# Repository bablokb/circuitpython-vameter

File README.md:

Project circuitpython-vameter
=============================

News
----

  - 06/2025: added support for INA3221.<br>
    Changed configuration-setup (incompatible, see below)<br>
    Changed support for ESP-01S (see [ESP-01S logging HowTo](doc/esp01logger.md))
  - 02/2025: added support for recording gpio-state during sampling
  - 01/2025: added support for DataProvider-specific configuration screens
  - 02/2024: added support for logging to SD-card
  - 10/2023: added support for INA260

Overview
--------

This repository contains the necessary CircuitPyhon software to drive a
voltage/current meter based on the following components:

  - INA3221 current-sensor breakout or
  - INA219 current-sensor breakout or
  - INA260 current-sensor breakout
  - Mini OLED display with 128x64 (based on a SSD1306-chip) or
  - SPI TFT-1.8" display (based on a ST7735R-chip)
  - 4x3 touchpad (based on a MPR121-chip)

Measurements are shown on the display and written as CSV to the
console.

Note that the display and touchpad are not strictly necessary. In
this case (i.e. you only want to measure voltage/current)
you have to change configuration values directly within the source-code.

If you want to use other components (especially a bigger display or
knobs and buttons instead of the touchpad) you should read the
[hacking guide](doc/hacking.md).

Also the main program is agnostic about which kind of sensor is
sampled. Just by providing a data-provider class you can collect data of any
sensor. This is also documented in the [hacking guide](doc/hacking.md).

Hardware
--------

All components use I2C except if you choose to use the SPI-display.
Connect the respective SDA, SCL, Vcc and GND
pins with the relevant pins of the MCU. Don't forget pullups, the builtin
pullups of the MCU are usually too weak.

On the left edge: the MCU, a RP2040-Qt-Trinkey. The INA219 is left to the
barrel-jack on the upper-left side of the breadboard. On the top edge
of the image is a load-resistor. In real applications this resistor is
replaced by the load you want to measure.

The mini-oled with 128x64 pixels is in the middle, on the right is a
MPR121-based keypad with 12 keys. A template for the key-mapping is in
`doc/keypad-template.png` and `doc/keypad-template.odg`.
The latter also has a version for horizontal orientation.

The INA219-breakout has two pins (next to the I2C-interface) and a
screw-terminal for attachement of the power-source (V+) and the load (V-).
**Don't use the pins, use the screw-terminal** or else your results will
be off by about 20%.

The INA260 offers a larger measurment-range than the INA219 (up to 36V/15A
compared to 32V/2A), but is more expensive and the resolution is a
tad worse. See the relevant tutorials and datasheets for details.

The INA3221 is a three-channel chip and measures up to 26V/3.2A with a
resolution of 0.4mA.

Installation (Pico or other MCU)
--------------------------------

Steps:

  0. Install the current version of CircuitPython to your device

  1. Install the following libraries from the CircuitPython library-bundle to
     the `lib`-directory of your device  

       - adafruit_bitmap_font
       - adafruit_bus_device
       - adafruit_connection_manager
       - adafruit_display_shapes
       - adafruit_display_text
       - adafruit_displayio_ssd1306
       - adafruit_ina219
       - adafruit_ina260
       - adafruit_ina3221
       - adafruit_mpr121
       - adafruit_register
       - adafruit_requests
       - adafruit_st7735r
       - adafruit_ticks
       - asyncio

     The preferred way to do this is to use `circup` (note that the device
     must be mounted):  

         sudo apt-get -y install pip3
         sudo pip3 install circup
         circup --path /mountpoint/of/device install -r requirements.txt

  2. Clone the repository

  3. Configure the software for your board and preferences. See
     [Configuration](#configuration) below.

  4. Check `src/lib/INA219DataProvider.py` for the correct voltage range.
     The code uses the library-default of 32V/2A, but this can be changed
     to 16V/1A or 16V/400mA. The additional precision is probably not
     worth the effort. Also, you can change the chip-internal oversampling
     of the ADC. The Default uses 8x oversampling resulting in a minimal
     sampling time of 4.26ms. Defaults for the INA260 are in
     `src/lib/INA260DataProvider.py`

  5. Copy all files from below `src` to your device.

Installation (Raspberry Pi)
---------------------------

There is a native build of CircuitPython for the Raspberry Pi, but that
build is extremely slow and not usable yet. The better option is to
use _Blinka_, an emulation layer which provides classes and methods usually
missing in a native python installation. Blinka runs on various SBCs,
the Raspberry Pi is only the most prominent example.

You can install the project on a Raspberry Pi (or any other Debian-based SBC
with Blinka-support) using:

    sudo tools/install-pi

This installs the project files, Blinka and all necessary libraries to
`/usr/local/cp-vameter`. To run the program, just use the command
`cp-vameter`. This assumes that `/usr/local/bin` is within your path.

Note that the installation is quite slow, because the install-command
installs everything to a python-virtenv. Especially download, compile
and install of numpy takes a lot of time, even on the faster Pis. For
running the program, a Pi-Zero is more than sufficient.

Also note that Blinka currently only supports SPI-displays with 16-bit
colors.

Configuration
-------------

Configuration is done using variables from three different files:

  - `src/<board_id>/board_config.py`: board-specific pins
  - `src/def_config.py`: default values
  - `src/user_config.py`: user-specific overrides

A board-specific configuration file is usually not necessary. There
are some seldom cases where the board uses different names for some
pins (e.g. `board.SCLK` instead of `board.SCK`). In this case a
board-specifc file is necessary. Other cases could be boards with
hard-wired displays/SD-slots that use specific pins for these
peripherals.

This repository has support-files for a number of platforms. If you use
a different MCU and that MCU does not provide the default pins, you should
create a directory `src/<board_id>` with a file `board_config.py`. Please
also create a pull-request in this case. `<board_id>` is the value
of `board.board_id` which you can query in the REPL after importing
the board-module.

The user-specific configuration file `src/user_config.py` is not part
of the repository. Copy `src/def_config.py` and keep only variables
you actually change.

**Note: starting with version 04/2025, the format of the configuration
file has changed.** Be sure to update any exiting user-specific
configuration files to match the format of `src/def_config.py`.

Usage
-----

The program is in three modes: _ready_ (after power-on and reset),
_active_ and _config_. Possible transitions are _ready-active-ready_ and
_ready-config-ready_.

If no keypad is detected, the program runs exactly once using the
defaults defined in the configuration files.

To switch modes, use the keypad:

Keys in blue are valid for the ready-mode, keys in black during configuration
and keys in red during the active-mode.

If you run the program on a SBC using the Blinka-emulation, you can
also provide settings via commandline parameters. For a list of options
run

    cp-vameter -h

This is especially useful for headless operation, i.e. without display
and without keypad.

Ready-Mode
----------

The ready-mode displays the last measurement-results (switch by using the
"View"-button):

Use the "Start" or "Config"-buttons to start a measurement or to enter
configuration mode.

Config-Mode
-----------

Once the program is in configuration mode, you can enter various parameters:

  - **Int-Scale**: the scale of the sampling interval in ms/s/m/h/d  
    The values 1-5 on the keypad are mapped to these intervals
  - **Interval**: the sampling interval in the given scale  
    
  - **Duration**: the duration of the measurement. A value of zero
    will run the measurement until it is explicitly or implicitly stopped.
    The scale of the duration depends on the scale of the interval. E.g. a
    interval-scale of 'ms' (i.e. in milliseconds) will force a duration
    measured in seconds. For an interval-scale of 's' the duration-scale will
    be in minutes and so on.  
    
  - **Update**: update-interval of the screen in milliseconds. These updates
    slow down the sampling, so make sure this value is much larger than the
    value of `interval`. Setting the value to zero will disable
    updates of the display during measurement.  
    
  - **DataProvider specific Configuration**: additional configurations for
    the DataProvider in use.

The "Next"-button will navigate through the configuration screens, after the
last item the system switches back to ready-mode.

DataProvider specific configuration is available for:

  - [`INA219Dataprovider`](./doc/ina219-config.md)
  - [`INA260Dataprovider`](./doc/ina260-config.md)

Active-Mode
-----------

During active-mode the program continuously reads the sensor and collects
and displays data. Actual sampling starts as soon as the voltage and
current is above a default threshold (1V/0.5mA) and stops again once

  - the values drop again below these limits, or
  - the configured measurement duration is reached or
  - you press the "Stop"-button

Using the "View"-button you cycle through various views:

  - voltage and current  
    
  - elapsed time  
    
  - plot-view of voltage  
    
  - plot-view of current  

Recording State during Sampling
-------------------------------

To record application state during sampling, you need extra pins
that the application sets to high or low depending on the state. These
pins have to be connected to the driving MUC and should be operated in
push-pull mode by the device under test.

In addition, you need to set e.g.

    PINS_APP = [(board.GPx,1), (board.GPy,0)]

in your `src/user_config.py`. `board.GPx` and `board.GPy` are gpios of
the MCU running circuitpython-vameter, not the gpios of the device under
test.

The example uses one state-pins that is active high and a second that is
active low.

Tips and Tricks
---------------

The default configuration of the sensor uses 8x oversampling for the
internal ADC. This reduces noise. Sampling-time according to the
datasheet is 4.26ms. Using less oversampling or less precision you
can bring this down to below 1ms, but if you really need high-frequency
sampling in this range you should think about reimplementing the project
using an optimzed setup and probably C/C++.

Using a Pico, you can reach a minimal sampling interval of about 9.5ms
(about 5.4ms measured on a Pi3B+, about 6.6ms on a QT Py ESP32-S2).

Display-updates take about 330ms. During update, you loose all samples.
*Setting the update-interval to zero prevents data-loss*, but you
can't see the values during measurement. When the
sampling-interval is larger than 330ms, no data-loss occurs regardless
of display-updates.

During active measurement, the default setup not only displays the
values, but also plots of the data. This is also costly (in speed
and memory) and can be disabled in `src/user_config.py` with the constant
`DEF_PLOTS`.

Note that the plots _don't_ show all measured values, but only the values
during display-updates. I.e. the plots just show the values from the
normal value-view across time. If you sample at 100ms and the display
update is every second, you will see every tenth value.

For ex-post data-visualization, save the data from the serial output
to a file and then use the
[Python Datamonitor](https://github.com/bablokb/py-datamon) to create
a plot. A ready to use configuration-file is in
[doc/cp-vameter.json](./cp-vameter.json).

The INA219 provides voltage, current and power. The default configuration
does not sample power. If you need all three values, you can change
this within `lib/INA219DataProvider` (set `WITH_POWER=True`).

In this file you can also change some additional settings, e.g. sample
frequency and voltage/current range as well as the cutoff-values used
for detecting start and stop of measurements.

Logging via WLAN is possible either with native WIFI (for those boards
with builtin WIFI) or an additional ESP-01S MCU connected to the UART
of the device. For details, read the [ESP-01S logging
HowTo](doc/esp01logger.md).

If the program runs on an device with native WIFI you can use the
builtin wifi for data-logging. See [UDP logging
HowTo](doc/udplogger.md) for details.

You can also log to a file on a SD-card. Add the following line to
your `user_config.py`:

    from SDCardLogger import DataLogger

This is useful for autonomous long-term logging, e.g. when charging a
battery. Tested with a Qt-Py-RP2040 with SD-card BFF. Fastest logging
interval was 7ms.

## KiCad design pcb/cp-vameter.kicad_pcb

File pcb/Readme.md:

A PCB for the INA219 and INA260
===============================

In this directory you will find the KiCAD-files for a 10x10cm pcb
for the INA219 and the INA260. The latter is untested, since it
is currently not available. The pcb is symetrical, i.e. you either
add components for the INA219 (top-left, top and middle right) or
for the INA260.

The connectors on the top and bottom are for the OLED and the keypad.
Alternatively, you could add Grove-connectors.
You also have to solder the two pullup-resistors in the middle.

The image shows a pcb with INA219. On the left you _either_ connect
a suitable mcu (see below) on the top-left, _or_ you connect an external
mcu (or Pi) using an I2C-Grove-connector. In the image you can see
both options.

On the right side, you have three power inputs for the load (use only one):

  - a JST-PH2 connector for LiPos
  - DuPont jumper pins
  - a 5.5/2.1mm barrel jack

Below the power switch are two power connectors (connect one of them to
to the load):

  - an AKL-182 socket
  - DuPont jumper pins

The AKL-182 socket takes AKL-169 plugs. I use these with various adapter
wires, equiped e.g. with micro-USB, USB-C, JST-PH2 on the other end.

As an alternative, you could use plain 3.5mm screw-terminals.

The pcb was ordered using JLCPCB.

OpenSCAD-files for the case are available in the toplevel `3D`-directory.

Supported MCUs
--------------

The driving MCU can be added to the board if it uses the XIAO-standard.
Possible alternatives:

  - Adafruit QT Py RP2400
  - Adafruit QT Py ESP32-S2
  - Seeedstudio XIAO RP2400

The form-factor alone is not sufficient, the MCU must also have enough
RAM/flash to support the application.

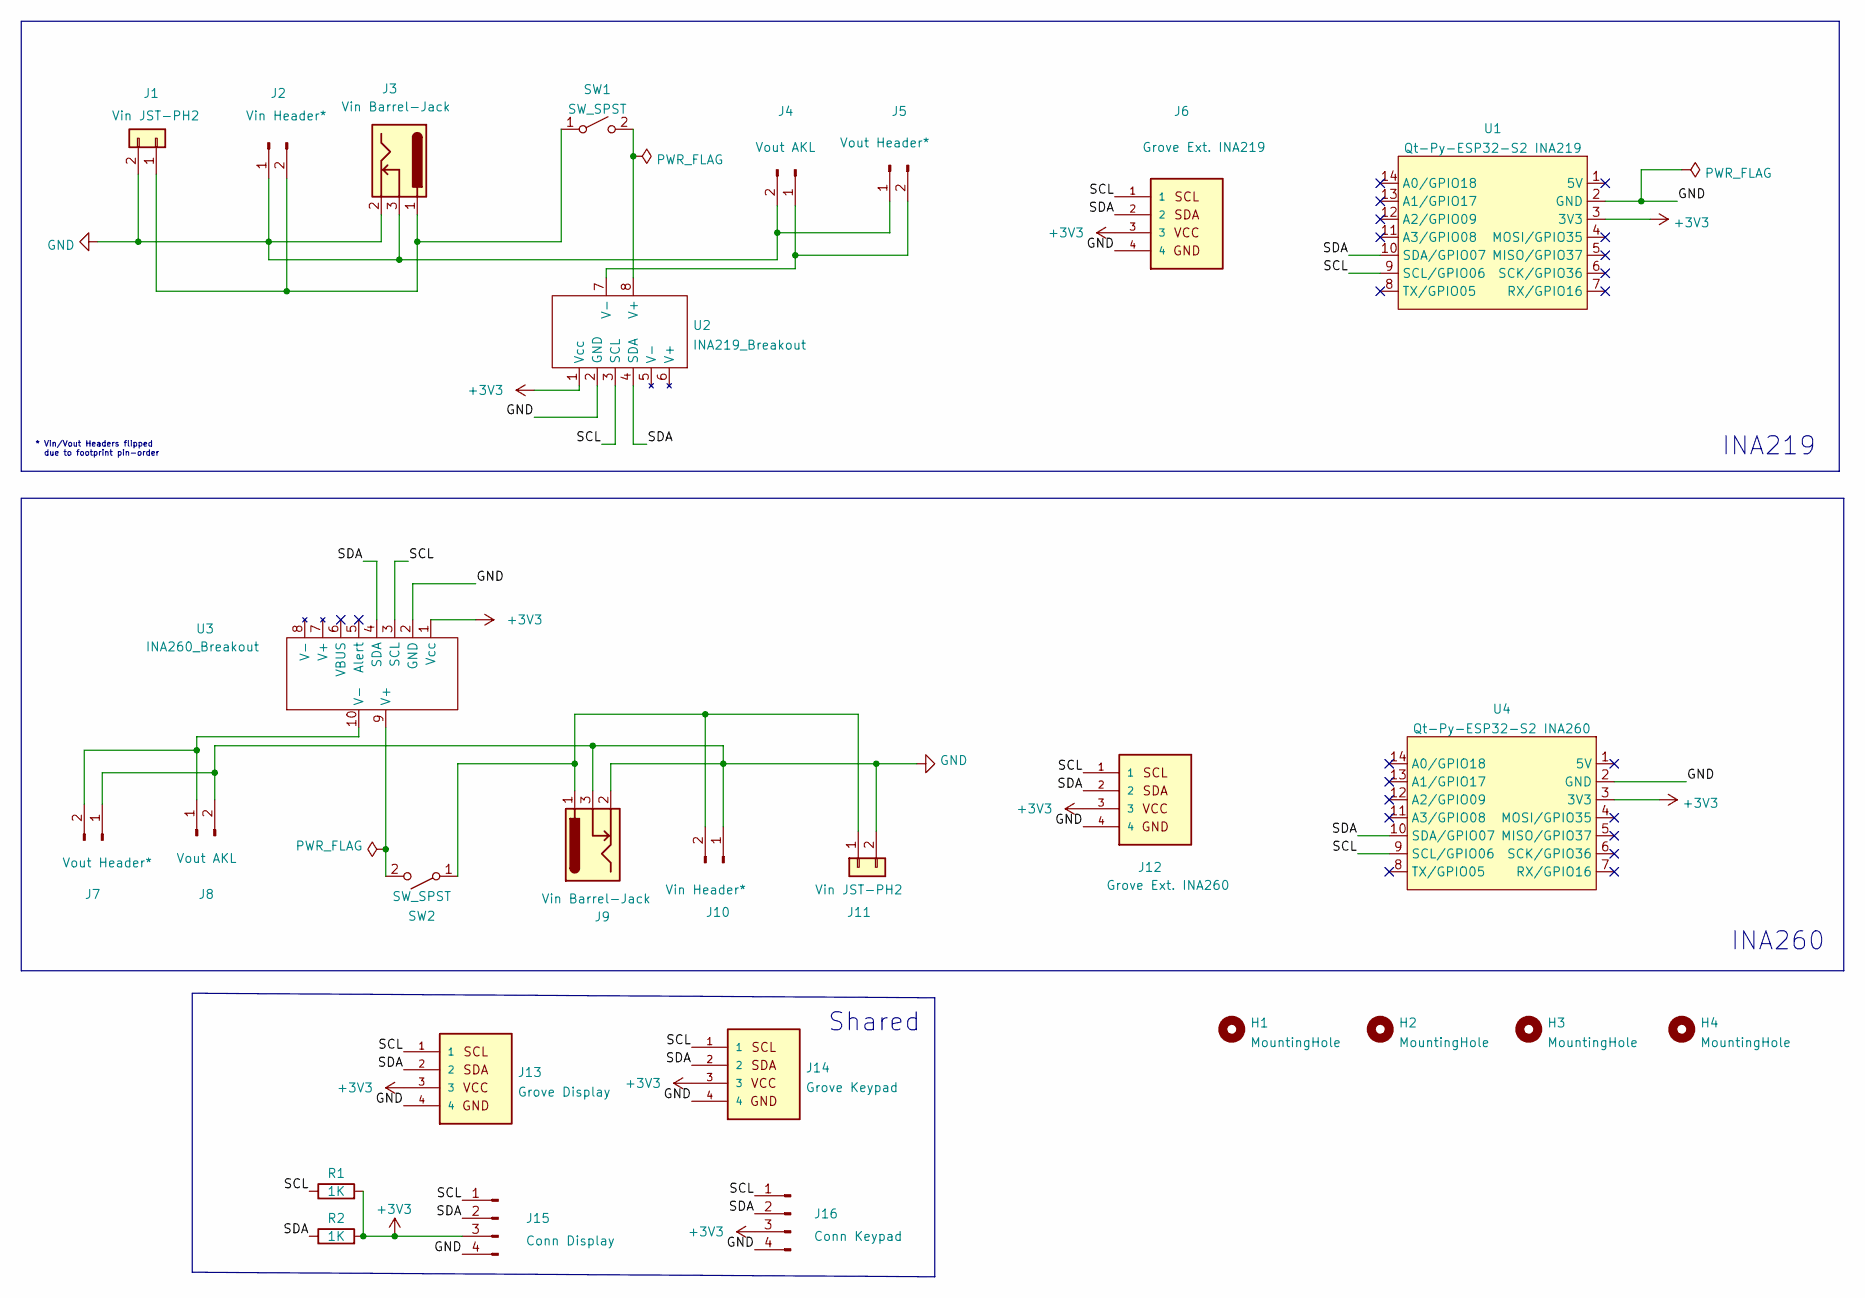
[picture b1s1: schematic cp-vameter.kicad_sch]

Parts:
H1, H2, H3, H4: MountingHole; MountingHole_2.5mm
J1, J11: Vin JST-PH2; JST_PH_S2B-PH-SM4-TB_1x02-1MP_P2.00mm_Horizontal
J2, J10: Vin Header*; PinHeader_1x02_P2.54mm_Horizontal
J3, J9: Vin Barrel-Jack; BarrelJack_CUI_PJ-102AH_Horizontal
J4, J8: Vout AKL; TerminalBlock_MetzConnect_Type182_PT11302HBBN_1x02_P3.50mm_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
J5, J7: Vout Header*; PinHeader_1x02_P2.54mm_Horizontal
J6: Grove Ext. INA219; grove_horizontal
J12: Grove Ext. INA260; grove_horizontal
J13: Grove Display; grove_horizontal
J14: Grove Keypad; grove_horizontal
J15: Conn Display; PinHeader_1x04_P2.54mm_Horizontal
J16: Conn Keypad; PinHeader_1x04_P2.54mm_Horizontal
R1, R2: 1K; R_1206_3216_Pad1.7x1.75mm_BB
SW1, SW2: SW_SPST; Kippschalter_On-Off
U1: Qt-Py-ESP32-S2 INA219; Qt-Py_ESP32-S2
U2: INA219_Breakout; INA219-Breakout
U3: INA260_Breakout; INA260-Breakout
U4: Qt-Py-ESP32-S2 INA260; Qt-Py_ESP32-S2

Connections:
+3V3: J6.3, J12.3, J13.3, J14.3, J15.3, J16.3, R1.2, R2.2, U1.3 (3V3), U2.1 (Vcc), U3.1 (Vcc), U4.3 (3V3)
/SCL: J6.1, J12.1, J13.1, J14.1, J15.1, J16.1, R1.1, U1.9 (SCL/GPIO06), U2.3 (SCL), U3.3 (SCL), U4.9 (SCL/GPIO06)
/SDA: J6.2, J12.2, J13.2, J14.2, J15.2, J16.2, R2.1, U1.10 (SDA/GPIO07), U2.4 (SDA), U3.4 (SDA), U4.10 (SDA/GPIO07)
GND: J1.2, J2.1, J3.2, J3.3, J4.2, J5.1, J6.4, J7.1, J8.2, J9.2, J9.3, J10.1, J11.2, J12.4, J13.4, J14.4, J15.4, J16.4, U1.2 (GND), U2.2 (GND), U3.2 (GND), U4.2 (GND)
unnamed: J1.1, J2.2, J3.1, SW1.1 (A)
unnamed: J4.1, J5.2, U2.7 (V-)
unnamed: J7.2, J8.1, U3.10 (V-)
unnamed: J9.1, J10.2, J11.1, SW2.1 (A)
unnamed: SW1.2 (B), U2.8 (V+)
unnamed: SW2.2 (B), U3.9 (V+)

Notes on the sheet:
* Vin/Vout Headers flipped due to footprint pin-order
Shared
INA260
INA219

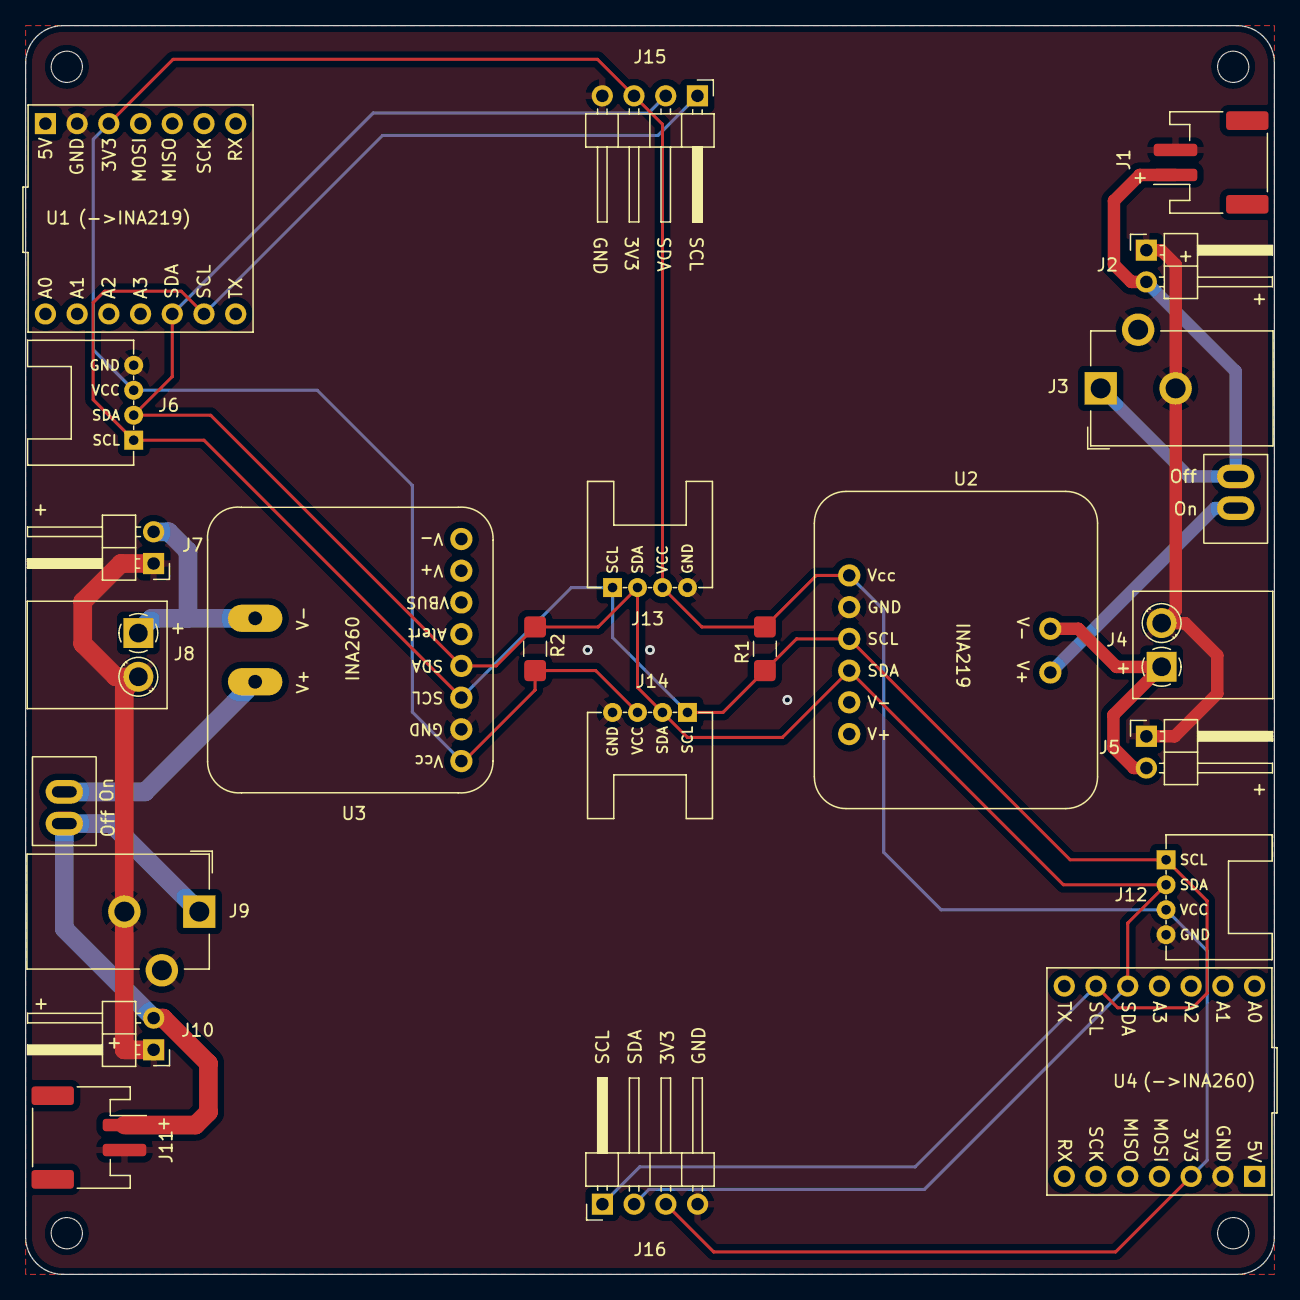
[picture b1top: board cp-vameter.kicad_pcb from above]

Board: 2 copper layers, 100.0 x 100.0 mm, 28 parts (0 on the bottom side), 10 nets.

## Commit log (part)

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2022-03-31 ignore only adafruit libs
2022-03-31 implement border-frame
2022-03-31 reduce border to 1 pixel
2022-03-31 added some early notes
2022-03-31 implemented ResultView
2022-03-31 add test for result view
2022-03-31 implemented ConfigView
2022-03-31 run(): temporarily return active
2022-03-31 refactored code to *State-classes
2022-04-01 use board.SDA and board.SCL if available
2022-04-01 updated overview and installation
2022-04-01 switch to pcf-fonts
2022-04-01 use board.DISPLAY if available
2022-04-01 refactoring: pass app to state-objects
2022-04-01 add settings-object
2022-04-01 use settings
2022-04-01 support headless-mode (make show() a noop)
2022-04-01 add results-attribute to class
2022-04-01 use results attribute
2022-04-01 basic implementation of run() with data-sampling and aggregation
2022-04-01 fix: use dummy width/height if there is no display
2022-04-01 don't release display for builtin displays
2022-04-01 fix logic for duration==0
2022-04-02 Revert "fix: use dummy width/height if there is no display"
    This reverts commit b8ebaaf30e9ce884e0ee4a8daaea5361fd6cf4c8.
2022-04-02 make all methods to noops if diplay is None
2022-04-02 create DataProvider object
2022-04-02 do nothing in headless-mode
2022-04-02 use data-provider from application
2022-04-02 add(): check for valid index
2022-04-02 added methods get_units() and reset()
2022-04-02 pass units to ValuesView, use DataProvider.reset()
2022-04-02 reorder data to support dynamic dimensions
2022-04-02 implement necessary changes because of changed DataAggregator
2022-04-02 support dynamic dimensions
2022-04-04 check key-events
2022-04-04 stop after 120 seconds
2022-04-04 check and process key-events
2022-04-04 add KeyEventProvider and fix i2c-in-use error
2022-04-05 refactored results-object
2022-04-05 record total-duration in results.time
2022-04-05 pass elapsed time to ValuesView
2022-04-05 write settings and results to log
2022-04-07 replace dummy implementation with working one
2022-04-07 implement handling of SHIFT-key
2022-04-07 switch units for 'update' from s to ms
2022-04-07 ConfigView: switch type of value from float to string
2022-04-07 KEYMAP_CONFIG: do not define SHIFT-key
2022-04-07 added elapsed-time view
2022-04-07 fixed links/title after rename of project
2022-04-07 added section 'Hardware'
2022-04-07 print duration at end of measurement
2022-04-07 catch error creating KeyEventProvider
2022-04-07 handle no KeyEventProvider
2022-04-07 reduce runtime from 120 to 60
2022-04-07 perform only a single measurement without keys
2022-04-08 fix headless operation
2022-04-08 add character 'O'
2022-04-08 add config-view for oversampling
2022-04-08 new implementation of sampling
2022-04-08 log total number of samples and samples/s
2022-04-08 added i2c as parameter for constructor
2022-04-08 switch to INA219DataProvider
2022-04-09 added adafruit_register to list of required libraries
2022-04-09 check update is not zero
2022-04-09 added link to image of hardware
2022-04-09 fixed markup
2022-04-12 minor markup fix
2022-04-13 fixed link to porting-guide
2022-04-13 implement PlotView
2022-04-13 add (single) PlotView
2022-04-13 don't throw StopIteration if duration is set
2022-04-15 add current value as label
2022-04-15 use single plot per dimension
2022-04-15 use tiny font (terminalio.FONT) for plot-label
2022-04-15 ValuesView: support up to 3 values
2022-04-15 support two or three values
2022-04-15 support output of supply-voltage
2022-04-15 don't start if current is below threshold
2022-04-15 support timeout while waiting for first sample
2022-04-19 added info about attaching power-source and load to the INA219
2022-04-19 add section about configuration of the INA219
2022-04-19 renamed file
2022-04-19 don't show supply-voltage
2022-04-21 refactor code to reuse debouncing
2022-04-21 add usage section
2022-04-21 updated image
2022-04-21 clear values at start
2022-04-21 add line-breaks before images
2022-04-26 disable auto-refresh, refresh in show()
2022-04-26 add code for performance-measurement
2022-04-27 output mean interval of measurement
2022-04-29 selectively disable plots
2022-04-29 add support for ST7735R-based SPI-displays
2022-04-30 added support for character 'W'
2022-04-30 define output-format for timestamp in ActiveState, not DataProvider
2022-04-30 support additional attribute 'power'
2022-04-30 added boot_out.txt
2022-04-30 support EXIT-key on Blinka
2022-04-30 define default pins for Raspberry Pi
2022-05-02 deactivate oversampling
2022-05-02 removed description of oversampling
2022-05-02 describe lib-install using circup
2022-05-02 added section about installation on a Pi
2022-05-05 don't sample power
2022-05-05 fix pin initialization
2022-05-05 additional notes about Pi installation
2022-05-06 improve layout for larger displays
2022-05-06 added keypad
2022-05-06 added *.stl
2022-05-06 added prototype keypad
2022-05-07 add support for multiple lines of text on keys
2022-05-07 reduced heigt of inset to 0.8
2022-05-16 refactored logging to SerialLogger
2022-05-17 renamed 'porting.md' to 'hacking.md'
2022-05-18 cleanup of unrelated wires
2022-05-20 add description of load-resistor
2022-05-20 mention INA260
2022-05-20 document use of terminalio.FONT
2022-05-21 enable static config of time-scale
2022-05-21 replace empty lines with comment-line
2022-05-21 refactored code to LogWriter
2022-05-23 document DEF_TM_SCALE
2022-05-23 changed interface (subclass must implement log())
2022-05-23 document logging with ESP-01S
2022-05-23 document DEF_PLOTS
2022-05-23 add note about alternative sensors
2022-05-23 replace fake-data in plot-examples
2022-05-23 changed values in view
2022-05-25 added pin-definitions for UART
2022-05-25 removed raise if no display is found
2022-05-25 added package libatlas-base-dev
2022-05-25 add spi to /boot/config.txt
2022-05-26 catch KeyboardInterrupt when running within Blinka
2022-05-26 add support for QT Py ESP32-S2
2022-05-26 set I2C-frequency to 400k
2022-05-26 only create venv if it does not yet exist
2022-05-26 add NL to all messages
2022-05-26 print msg without extra NL
2022-05-26 added additional libraries
2022-05-26 minor spelling fixes
2022-05-27 don't move files in lib to runtime
2022-05-28 Blinka: support cmdline-arguments
2022-05-30 various small updates
2022-05-30 bugfix: use time.sleep() instead just sleep()
2022-05-30 move disconnect to lib
2022-06-04 update timings
2022-06-04 change width
2022-06-04 without keypad, toggle result-views after measurement
2022-06-08 added option -e/--exit
2022-06-08 support exit-option for blinka-boards
2022-06-16 set current threshold to 0 and prevent negative current-values
2022-06-20 implemented asyncio-support
2022-06-20 added asyncio
2022-06-21 update view from within _show_view()
2022-06-22 optimize for stable sampling rate
2022-06-23 'update' is always a value in ms, regardless of scale
2022-06-23 update timings for Pi3B+
2022-06-24 update views only after a new sample
2022-06-24 support multiple scales for sampling-interval (ms,s,m,...)
2022-06-24 update only app-files, if called with arbitrary argument
2022-06-24 create new instance of ActiveState for every measurement
2022-06-27 document additional characters
2022-06-27 revert commit 8a935c9adb666bfe6fe5adc46522936f6f4903f7
2022-06-27 support runtime-configuration of interval-scale
2022-06-27 document runtime-configuration of interval-scale
2022-06-27 wakeup at least every second to process stop if necessary
2022-06-28 show plots also in ready-state
2022-07-05 minor spelling correction
2022-07-05 code cleanup: replaced 'tm_scale' with 'int_scale'
2022-07-05 code cleanup: replaced 'data_t0' with 'data_t_last'
2022-07-29 intial commit (Rev 1.0)
2022-08-01 removed code for inset
2022-08-03 renamed variables
2022-08-03 removed rim
2022-08-09 refactored constants to dimensions.scad
2022-08-10 changed thickness to base-thickness
2022-08-10 removed snaps / set base=1.6
2022-08-10 removed snaps
2022-08-11 removed snaps and optimized layout of oled/keypad
2022-08-11 add oled/keypad as part of module cover
2022-08-12 added w2-dimension
2022-08-12 added walls
2022-08-12 replaced tht-footprint with smd-footprint for JST-connector
2022-08-17 support landscape orientation of keypad
2022-08-17 switch to new sparkline implementation with dynamic x-pitch
2022-08-18 be more specific about adafruit-libs
2022-08-19 added src/user_config.py
2022-08-19 refactor configuration to def_config.py and board_config.py
2022-08-19 changed eol-char from CRLF to LF
2022-08-19 document new configuration-scheme
2022-08-19 updated to new lib-versions
2022-08-19 define (and use) config-variable for display-type
2022-08-19 install pip-packages in upgrade-mode
2022-08-26 override default-logger from user_config.py
2022-08-27 replaced tht-footprint with smd-footprint for JST-connector in pcb
2022-09-09 intial commit
2022-09-09 link to image of case
2022-09-09 add some more info about plots
2022-09-09 document cp-datalogger.py
2022-09-09 add info about OpenSCAD-files for case
2022-09-09 fix link to configuration-section
2023-10-27 fixed handling of reading from serial
2023-10-27 bugfix: set oversampling after set_calibration_xxx()
2023-10-30 added support for INA260
2023-11-03 changed width of plot to 1920
2024-02-22 removed version numbers, added adafruit_sdcard
2024-02-22 added support for two new boards
2024-02-22 implemented logging to SD-card
2024-02-22 fixed import statements
2024-02-22 don't raise exception if no user_config is found
2024-03-13 added option -C/--comments
2024-03-28 renamed directory due to changes in board-name
2024-12-18 add v_min/a_min to settings
2024-12-19 print exception when user-specific config-file cannot be loaded
2024-12-19 support DataProvider specific configuration-views
2025-01-05 added sample imports for DataProvider
2025-01-05 updated char-list
2025-01-05 added some chars to the fonts
2025-01-06 document new configuration-options
2025-01-06 only show plots if update for views is turned on
2025-01-06 fixed links
2025-01-06 fixed text
2025-02-15 add default for PINS_APP
2025-02-15 add PINS_APP to settings
2025-02-16 added comment for PINS_APP
2025-02-16 return a list instead of a tuple
2025-02-16 document configuration of state gpios
2025-02-17 add option -r: relative cumulative energy
2025-03-26 support sampling digitial IO pins
2025-03-26 fix syntax errors
2025-03-26 support user-settings from ValueHolder object
2025-03-26 py-datamon config-file for plot of cumulative energy
2025-03-26 refactoring: move all application code from lib to root-directory
2025-03-26 use sdcardio instead of adafruit_sdcard
2025-03-26 removed adafruit_sdcard from requirements.txt
2025-03-26 renamed ESP32Logger.py to UDPLogger.py
2025-03-26 replaced references to ESP32Logger with UDPLogger
2025-03-27 remove (direct) support of the ESP-01S
2025-03-27 update list of required libraries
2025-03-27 border attribute now in app.settings
2025-03-27 removed unused attribute self._border
2025-03-27 make I2C-address configurable
2025-03-28 fix syntax for CP 9.x
2025-03-28 added board-definition for Seeed-Studio XIAO-RP2040
2025-03-28 refactored configuration
2025-03-28 bugfix: wrong initialization of aggregator
2025-03-28 bugfix: wrong implementation of adding GPIO-data
2025-03-28 start all channels in disabled state
2025-03-28 don't create views if no display is available
2025-03-28 support 'settings.display = None'
2025-03-29 fixed format
2025-03-29 not needed, since defaults are fine
2025-03-30 added missing libraries to installation
2025-03-30 removed board-config for Pi Pico, since it is not board specific
2025-03-30 reduce to really board-specific configurations
2025-03-30 updated for version 04/2025
2025-04-08 fixed format (once more) and changed program defaults
2025-04-08 use default keys from board-module if not explicitely set
2025-06-13 print exceptions raised by import from user_config
2025-06-13 migrate to CP9 displayio modules (i2cdisplaybus, fourwire)
2025-06-13 change defaults to be within 5ms limit (and update comments in INA3221DataProvider.py)
2025-06-13 new option: -c/--columns to set the number of columns
2025-06-14 add example for INA3221
2025-06-16 updated section 'News'
2025-06-16 support INA3221-format with three channels
2026-03-03 bugfix: use shared-spi and pass cs as Pin
